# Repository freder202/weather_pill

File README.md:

### A small and compact weather logging station to use for outdoor adventures

The goal is to log the temperature, humidity, while having it displayed on a small lcd 

The battery life is expected to be 2 years on a CR2032

This is the Rev2, which is currently being tested as of August 2025

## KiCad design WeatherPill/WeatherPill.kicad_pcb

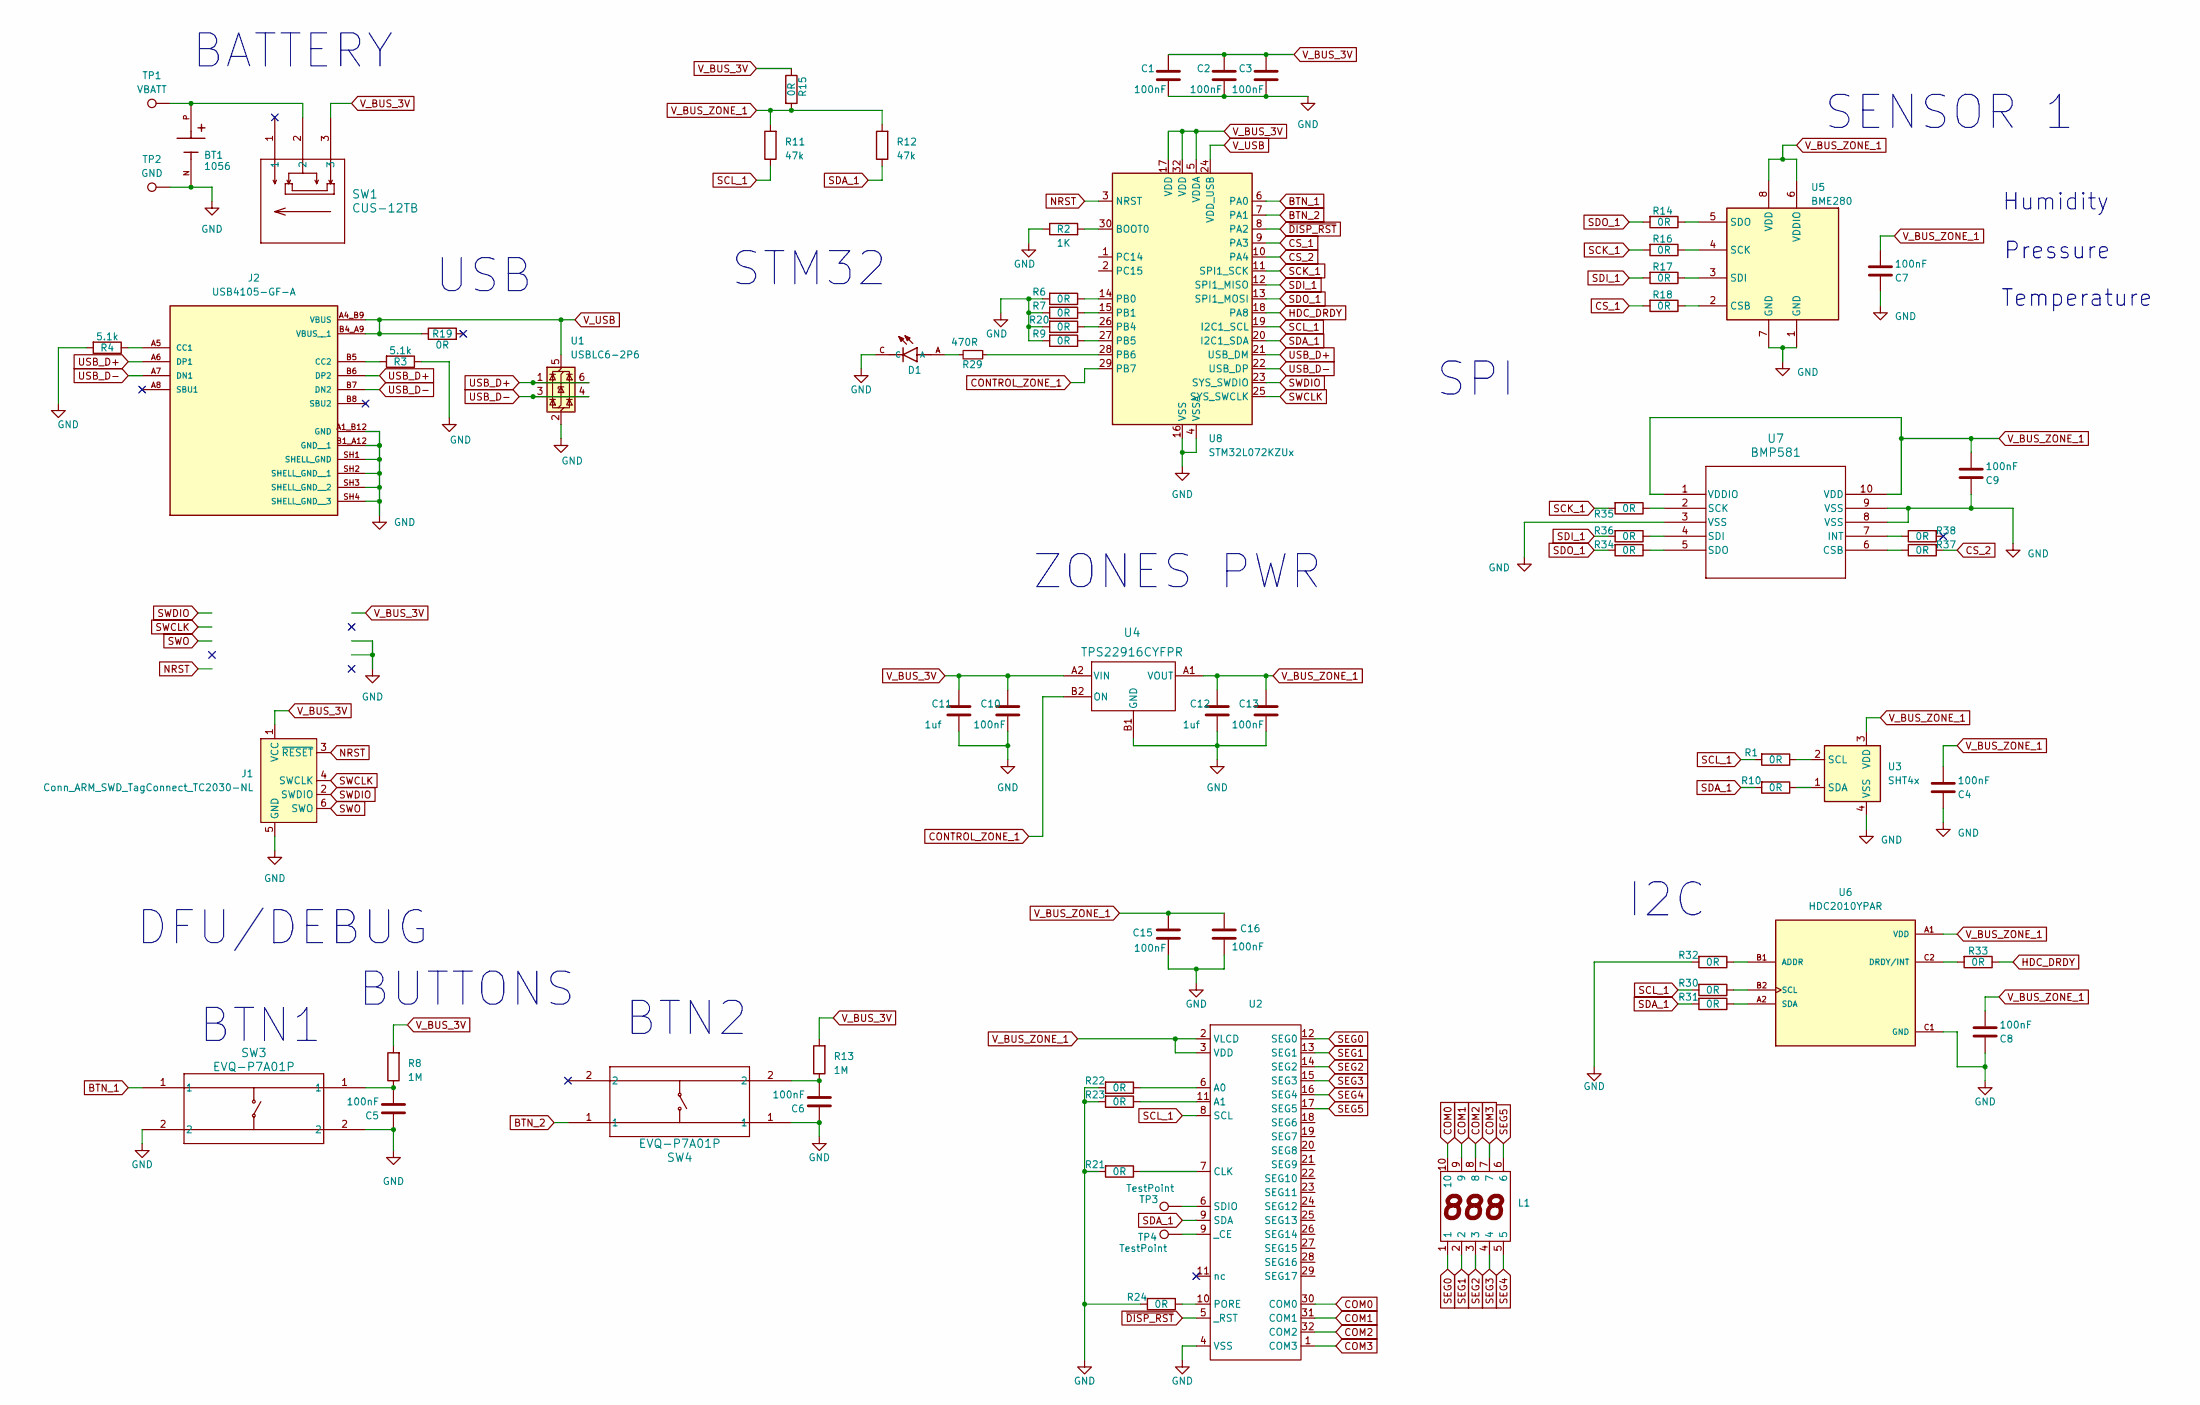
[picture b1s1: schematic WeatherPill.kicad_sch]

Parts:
BT1: 1056; BAT_1056; PARTREV D
C1, C2, C3, C4, C5, C6, C7, C8, C9, C10, C13, C15, C16: 100nF; LED_0402_1005Metric_Pad0.77x0.64mm_HandSolder
C11, C12: 1uf; LED_0402_1005Metric_Pad0.77x0.64mm_HandSolder
D1: LTST-C190GKT; LEDM1608X80
J1: Conn_ARM_SWD_TagConnect_TC2030-NL; Tag-Connect_TC2030-IDC-NL_2x03_P1.27mm_Vertical
J2: USB4105-GF-A; GCT_USB4105-GF-A; PARTREV B4
L1: INND-SS30
R1, R6, R7, R9, R10, R14, R15, R16, R17, R18, R19, R20, R21, R22, R23, R24, R30, R31, R32, R33, R34, R35, R36, R37, R38: 0R; R_0201_0603Metric_Pad0.64x0.40mm_HandSolder
R2: 1K; R_0201_0603Metric_Pad0.64x0.40mm_HandSolder
R3, R4: 5.1k; R_0201_0603Metric_Pad0.64x0.40mm_HandSolder
R8, R13: 1M; R_0201_0603Metric_Pad0.64x0.40mm_HandSolder
R11, R12: 47k; R_0201_0603Metric_Pad0.64x0.40mm_HandSolder
R29: 470R; R_0201_0603Metric_Pad0.64x0.40mm_HandSolder
SW1: CUS-12TB; CUS-12TB_NDC
SW3, SW4: EVQ-P7A01P; EVQ_P7_PAN
TP1: VBATT; TestPoint_Pad_D1.5mm
TP2: GND; TestPoint_Pad_D1.5mm
TP3, TP4: TestPoint
U1: USBLC6-2P6; SOT-666
U2: HVQFN-32-1EP_5x5mm_P0.5mm_EP3.1x3.1mm
U3: SHT4x; Sensirion_DFN-4_1.5x1.5mm_P0.8mm_SHT4x_NoCentralPad
U4: TPS22916CYFPR; YFP0004ABAB
U5: BME280; Bosch_LGA-8_2.5x2.5mm_P0.65mm_ClockwisePinNumbering
U6: HDC2010YPAR; BGA6C100X50P2X3_HDC2010YPAR; PARTREV C
U7: BMP581; QFN10_BMP581_BOS-M
U8: STM32L072KZUx; QFN-32-1EP_5x5mm_P0.5mm_EP3.45x3.45mm

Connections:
COM0: L1.10, U2.30 (COM0)
COM1: L1.9, U2.31 (COM1)
COM2: L1.8, U2.32 (COM2)
COM3: L1.7, U2.1 (COM3)
CONTROL_ZONE_1: U4.B2 (ON), U8.29 (PB7)
CS_1: R18.2, U8.9 (PA3)
CS_2: R37.2, U8.10 (PA4)
HDC_DRDY: R33.1, U8.18 (PA8)
NRST: J1.3 (~RESET), U8.3 (NRST)
unnamed: BT1.P, SW1.2, TP1.1
unnamed: C6.2, R13.1, SW4.2
unnamed: D1.A, R29.2
unnamed: J2.A5 (CC1), R4.1
unnamed: J2.B5 (CC2), R3.2
unnamed: R22.1, TP3.1, U2.6 (A0)
unnamed: R23.1, U2.11 (A1)
unnamed: R21.1, U2.7 (CLK)
unnamed: R24.1, U2.10 (PORE)
unnamed: R1.1, U3.2 (SCL)
unnamed: R10.1, U3.1 (SDA)
unnamed: R18.1, U5.2 (CSB)
unnamed: R16.1, U5.4 (SCK)
unnamed: R17.1, U5.3 (SDI)
unnamed: R14.1, U5.5 (SDO)
unnamed: R32.1, U6.B1 (ADDR)
unnamed: R33.2, U6.C2 (DRDY/INT)
unnamed: R30.1, U6.B2 (SCL)
unnamed: R31.1, U6.A2 (SDA)
unnamed: R37.1, U7.6 (CSB)
unnamed: R38.1, U7.7 (INT)
unnamed: R35.1, U7.2 (SCK)
unnamed: R36.1, U7.4 (SDI)
unnamed: R34.1, U7.5 (SDO)
unnamed: R2.2, U8.30 (BOOT0)
unnamed: R6.1, U8.14 (PB0)
unnamed: R7.1, U8.15 (PB1)
unnamed: R20.1, U8.26 (PB4)
unnamed: R9.1, U8.27 (PB5)
unnamed: R29.1, U8.28 (PB6)
SCK_1: R16.2, R35.2, U8.11 (SPI1_SCK)
SCL_1: R1.2, R11.1, R30.2, U2.8 (SCL), U8.19 (I2C1_SCL)
SDI_1: R17.2, R36.2, U8.12 (SPI1_MISO)
SDO_1: R14.2, R34.2, U8.13 (SPI1_MOSI)
SEG0: L1.1, U2.12 (SEG0)
SEG1: L1.2, U2.13 (SEG1)
SEG2: L1.3, U2.14 (SEG2)
SEG3: L1.4, U2.15 (SEG3)
SEG4: L1.5, U2.16 (SEG4)
SEG5: L1.6, U2.17 (SEG5)
SWCLK: J1.4 (SWCLK), U8.25 (SYS_SWCLK)
SWDIO: J1.2 (SWDIO), U8.23 (SYS_SWDIO)
SWO: J1.6 (SWO)
USB_D+: J2.A6 (DP1), J2.B6 (DP2), U1.1 (I/O1), U1.6 (I/O1), U8.21 (USB_DM)
USB_D-: J2.A7 (DN1), J2.B7 (DN2), U1.3 (I/O2), U1.4 (I/O2), U8.22 (USB_DP)
V_BUS_3V: C1.1, C2.1, C3.1, C10.1, C11.1, J1.1 (VCC), R8.2, R13.2, R15.1, SW1.3, U4.A2 (VIN), U8.5 (VDDA), U8.17 (VDD), U8.32 (VDD)
V_BUS_ZONE_1: C4.2, C7.2, C8.2, C9.2, C12.1, C13.1, C15.1, C16.1, R11.2, R12.2, R15.2, U2.2 (VLCD), U2.3 (VDD), U3.3 (VDD), U4.A1 (VOUT), U5.6 (VDDIO), U5.8 (VDD), U6.A1 (VDD), U7.1 (VDDIO), U7.10 (VDD)
V_USB: J2.A4_B9 (VBUS), J2.B4_A9 (VBUS__1), R19.1, U1.5 (VBUS), U8.24 (VDD_USB)
~DISP_RST: U2.5 (_RST), U8.8 (PA2)

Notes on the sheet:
DFU/DEBUG
Pressure
ZONES PWR
I2C
BTN1
Temperature
USB
BTN2
SPI
STM32
BATTERY
SENSOR 1
BUTTONS
Humidity

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
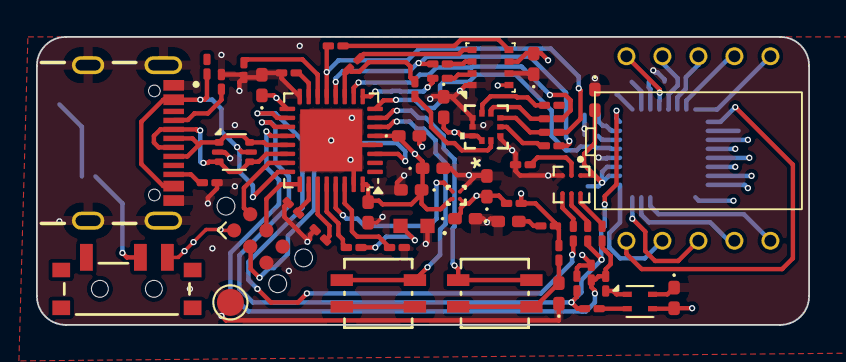
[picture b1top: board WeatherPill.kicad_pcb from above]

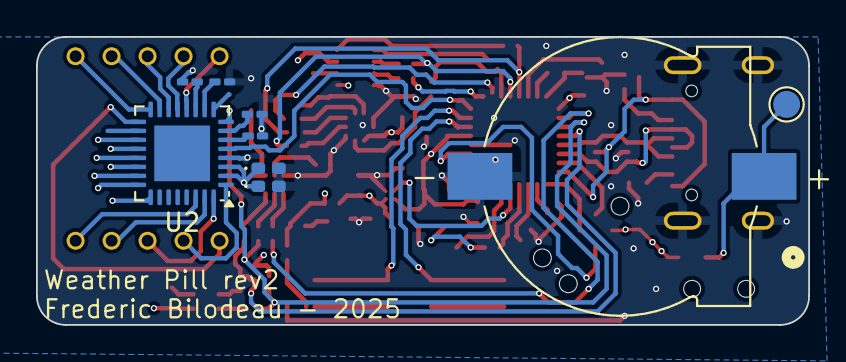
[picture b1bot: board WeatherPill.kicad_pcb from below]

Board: 4 copper layers, 42.9 x 16.0 mm, 66 parts (9 on the bottom side), 62 nets.

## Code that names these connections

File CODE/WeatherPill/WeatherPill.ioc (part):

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Mcu.Name=STM32L052K(6-8)Tx
Mcu.Package=LQFP32
Mcu.UserName=STM32L052K8Tx
PA11.Mode=Device
PA11.Signal=USB_DM
PA12.Mode=Device
PA12.Signal=USB_DP
PA13.Mode=Serial_Wire
PA13.Signal=SYS_SWDIO
PA14.Mode=Serial_Wire
PA14.Signal=SYS_SWCLK
PA3.GPIOParameters=GPIO_Label
PA3.GPIO_Label=CS_1
PA3.Signal=GPIO_Output
PA4.GPIOParameters=GPIO_Label
PA4.GPIO_Label=CS_2
PA4.Signal=GPIO_Output
PA5.Mode=Full_Duplex_Master
PA5.Signal=SPI1_SCK
PA6.Mode=Full_Duplex_Master
PA6.Signal=SPI1_MISO
PA7.Mode=Full_Duplex_Master
PA7.Signal=SPI1_MOSI
PA8.GPIOParameters=GPIO_Label
PA8.GPIO_Label=BTN_1
PA8.Signal=GPXTI8
PA9.GPIOParameters=GPIO_Label
PA9.GPIO_Label=BTN_0
PA9.Signal=GPXTI9
PB3.GPIOParameters=GPIO_Label
PB3.GPIO_Label=CTRL_Z_3
PB3.Signal=GPIO_Output
PB4.GPIOParameters=GPIO_Label
PB4.GPIO_Label=CTRL_Z_2
PB4.Signal=GPIO_Output
PB5.GPIOParameters=GPIO_Label
PB5.GPIO_Label=CTRL_Z_1
PB5.Signal=GPIO_Output
PB6.Mode=I2C
PB6.Signal=I2C1_SCL
PB7.Mode=I2C
PB7.Signal=I2C1_SDA
RCC.SYSCLKFreq_VALUE=16000000
RCC.SYSCLKSource=RCC_SYSCLKSOURCE_HSI
board=custom

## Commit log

2023-04-29 init
2023-04-29 stating to configs pins
2023-06-12 in review
2023-06-15 roasting
2024-05-16 revision 2
2024-06-13 fred: update pcb
2024-06-27 fred: avancements
2025-08-07 V2 cooking
2025-08-30 rev 2 sent
2025-08-30 errata sent v2
